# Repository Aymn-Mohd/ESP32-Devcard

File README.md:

# ESP32DevCard v1 — Credit-Card Sized Powerhouse

A deployment-oriented ESP32-S3 development board for engineers building systems, not desk toys. Real power delivery, integrated sensing, and full breakout in a compact 70 × 50 mm footprint.

The goal: eliminate the wiring mess that causes 80% of prototype failures.

---

## Why This Exists

Most ESP32 boards assume your prototype ends at a breadboard. The moment you attach motors, LED arrays, or anything drawing real current, they fall apart.

This solves that problem directly:

* 4-layer stackup for signal and power integrity
* Multiple power injection points
* Clean grounding discipline and ESD protection
* On-board peripheral support for validation without external modules

This is the board you use when reliability matters from the first test.

---

## Core Capabilities

* ESP32-S3-MINI-1-N8 (Wi-Fi + BLE, dual core)
* ENS210 temperature/humidity sensor (I²C)
* WS2812B RGB indicator (GPIO48)
* USB-C for power/programming with protection circuitry
* 44 usable GPIOs on dual headers
* High-current 5V and 3.3V rails
* 4-layer PCB for controlled return paths

---

## Technical Specifications

| Parameter         | Value            |
| ----------------- | ---------------- |
| Dimensions        | 70 × 50 mm       |
| Layers            | 4                |
| MCU Flash         | 8 MB             |
| Operating Voltage | 3.3 V            |
| Status LED        | WS2812B (GPIO48) |
| On-board Sensor   | ENS210           |

---

## Getting Started

1. Plug in via USB-C
2. Flash using the ESP-IDF toolchain or PlatformIO
3. Access peripherals immediately (I²C sensor, indicator LED)

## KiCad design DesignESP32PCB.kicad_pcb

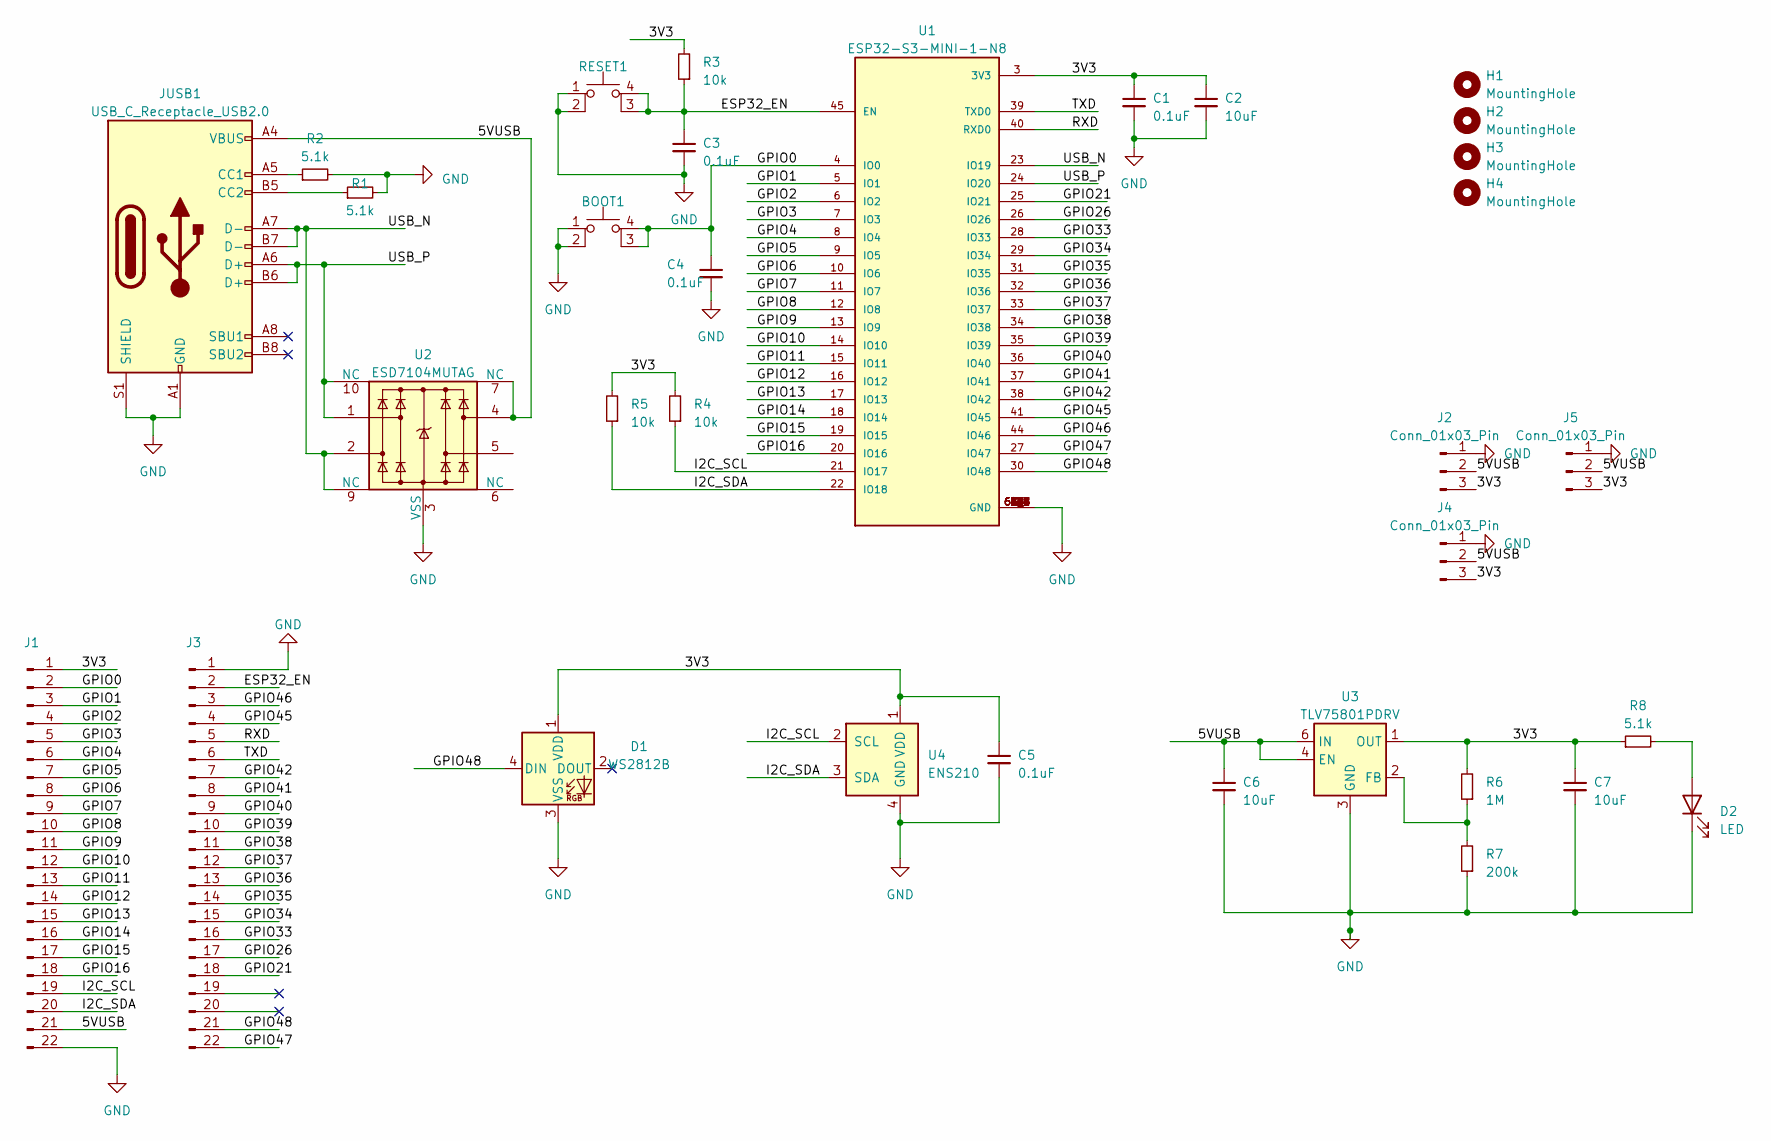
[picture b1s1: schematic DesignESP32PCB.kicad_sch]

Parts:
BOOT1: SW_SPST_PTS810
C1, C3, C4, C5: 0.1uF; C_0603_1608Metric
C2, C6, C7: 10uF; C_0603_1608Metric
D1: WS2812B; LED_WS2812B_PLCC4_5.0x5.0mm_P3.2mm
D2: LED; LED_0603_1608Metric
H1, H2, H3, H4: MountingHole; MountingHole_2.2mm_M2_Pad_Via
J1, J3: PinHeader_1x22_P2.54mm_Vertical
J2, J4, J5: Conn_01x03_Pin; PinHeader_1x03_P2.54mm_Vertical
JUSB1: USB_C_Receptacle_USB2.0; USB_C_Receptacle_GCT_USB4105-xx-A_16P_TopMnt_Horizontal
R1, R2, R8: 5.1k; R_0603_1608Metric
R3, R4, R5: 10k; R_0603_1608Metric
R6: 1M; R_0603_1608Metric
R7: 200k; R_0603_1608Metric
RESET1: SW_SPST_PTS810
U1: ESP32-S3-MINI-1-N8; XCVR_ESP32-S3-MINI-1-N8; PARTREV v0.6
U2: ESD7104MUTAG; Diodes_UDFN-10_1.0x2.5mm_P0.5mm
U3: TLV75801PDRV; WSON-6-1EP_2x2mm_P0.65mm_EP1x1.6mm
U4: ENS210; AMS_QFN-4-1EP_2x2mm_P0.95mm_EP0.7x1.6mm

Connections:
/3V3: C1.1, C2.1, C5.1, C7.1, D1.1 (VDD), J1.1, J2.3, J4.3, J5.3, R3.2, R4.2, R5.2, R6.2, R8.1, U1.3 (3V3), U3.1 (OUT), U4.1 (VDD)
/5VUSB: C6.1, J1.21, J2.2, J4.2, J5.2, JUSB1.A4 (VBUS), JUSB1.A9 (VBUS), JUSB1.B4 (VBUS), JUSB1.B9 (VBUS), U2.4, U2.7 (NC), U3.4 (EN), U3.6 (IN)
/ESP32_EN: C3.1, J3.2, R3.1, RESET1.3 (K), RESET1.4 (A), U1.45 (EN)
/GPIO0: BOOT1.3 (K), BOOT1.4 (A), C4.1, J1.2, U1.4 (IO0)
/GPIO1: J1.3, U1.5 (IO1)
/GPIO2: J1.4, U1.6 (IO2)
/GPIO3: J1.5, U1.7 (IO3)
/GPIO4: J1.6, U1.8 (IO4)
/GPIO5: J1.7, U1.9 (IO5)
/GPIO6: J1.8, U1.10 (IO6)
/GPIO7: J1.9, U1.11 (IO7)
/GPIO8: J1.10, U1.12 (IO8)
/GPIO9: J1.11, U1.13 (IO9)
/GPIO10: J1.12, U1.14 (IO10)
/GPIO11: J1.13, U1.15 (IO11)
/GPIO12: J1.14, U1.16 (IO12)
/GPIO13: J1.15, U1.17 (IO13)
/GPIO14: J1.16, U1.18 (IO14)
/GPIO15: J1.17, U1.19 (IO15)
/GPIO16: J1.18, U1.20 (IO16)
/GPIO21: J3.18, U1.25 (IO21)
/GPIO26: J3.17, U1.26 (IO26)
/GPIO33: J3.16, U1.28 (IO33)
/GPIO34: J3.15, U1.29 (IO34)
/GPIO35: J3.14, U1.31 (IO35)
/GPIO36: J3.13, U1.32 (IO36)
/GPIO37: J3.12, U1.33 (IO37)
/GPIO38: J3.11, U1.34 (IO38)
/GPIO39: J3.10, U1.35 (IO39)
/GPIO40: J3.9, U1.36 (IO40)
/GPIO41: J3.8, U1.37 (IO41)
/GPIO42: J3.7, U1.38 (IO42)
/GPIO45: J3.4, U1.41 (IO45)
/GPIO46: J3.3, U1.44 (IO46)
/GPIO47: J3.22, U1.27 (IO47)
/GPIO48: D1.4 (DIN), J3.21, U1.30 (IO48)
/I2C_SCL: J1.19, R4.1, U1.21 (IO17), U4.2 (SCL)
/I2C_SDA: J1.20, R5.1, U1.22 (IO18), U4.3 (SDA)
/RXD: J3.5, U1.40 (RXD0)
/TXD: J3.6, U1.39 (TXD0)
/USB_N: JUSB1.A7 (D-), JUSB1.B7 (D-), U1.23 (IO19), U2.2, U2.9 (NC)
/USB_P: JUSB1.A6 (D+), JUSB1.B6 (D+), U1.24 (IO20), U2.1, U2.10 (NC)
GND: BOOT1.1, BOOT1.2, C1.2, C2.2, C3.2, C4.2, C5.2, C6.2, C7.2, D1.3 (VSS), D2.1 (K), J1.22, J2.1, J3.1, J4.1, J5.1, JUSB1.A1 (GND), JUSB1.A12 (GND), JUSB1.B1 (GND), JUSB1.B12 (GND), JUSB1.S1 (SHIELD), R1.2, R2.2, R7.1, RESET1.1, RESET1.2, U1.1 (GND), U1.2 (GND), U1.42 (GND), U1.43 (GND), U1.46 (GND), U1.47 (GND), U1.48 (GND), U1.49 (GND), U1.50 (GND), U1.51 (GND), U1.52 (GND), U1.53 (GND), U1.54 (GND), U1.55 (GND), U1.56 (GND), U1.57 (GND), U1.58 (GND), U1.59 (GND), U1.60 (GND), U1.61 (GND), U1.61_1 (GND), U1.61_2 (GND), U1.61_3 (GND), U1.61_4 (GND), U1.61_5 (GND), U1.61_6 (GND), U1.61_7 (GND), U1.61_8 (GND), U1.62 (GND), U1.63 (GND), U1.64 (GND), U1.65 (GND), U2.3 (VSS), U2.8 (VSS), U3.3 (GND), U3.7 (GND), U4.4 (GND), U4.5 (GND)
unnamed: D2.2 (A), R8.2
unnamed: JUSB1.A5 (CC1), R2.1
unnamed: JUSB1.B5 (CC2), R1.1
unnamed: R6.1, R7.2, U3.2 (FB)

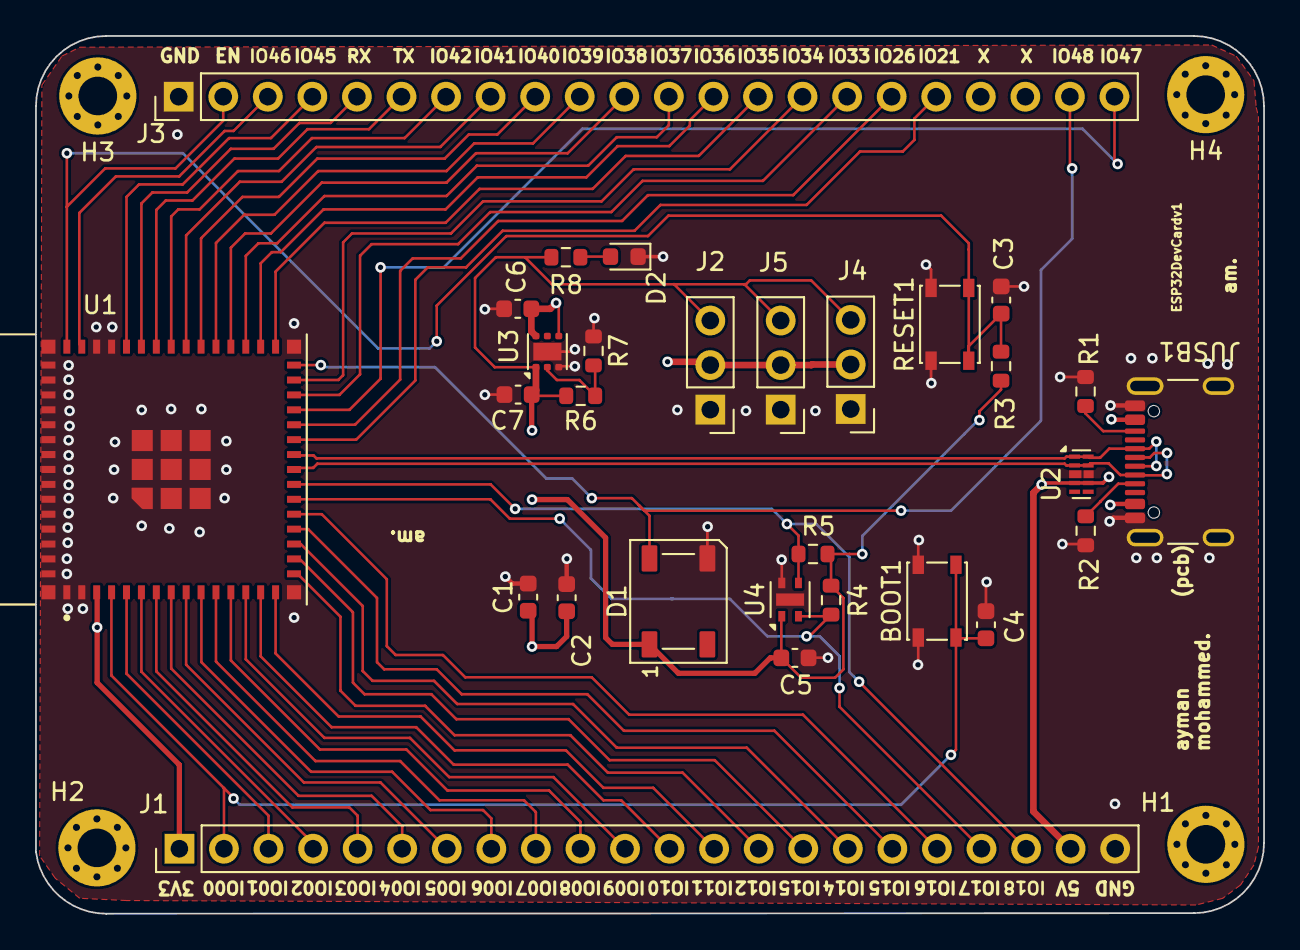
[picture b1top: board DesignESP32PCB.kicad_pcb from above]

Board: 4 copper layers, 70.0 x 50.0 mm, 33 parts (0 on the bottom side), 47 nets.

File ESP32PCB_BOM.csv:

Reference,Qty,Part#,Value,Footprint
U1,1,ESP32-S3-MINI-1-N8,-,ESP32-S3-MINI-1-N8:XCVR_ESP32-S3-MINI-1-N8
U2,1,ESD7104MUTAG,-,Package_DFN_QFN:Diodes_UDFN-10_1.0x2.5mm_P0.5mm
U3,1,TLV75801PDRVR,-,Package_SON:WSON-6-1EP_2x2mm_P0.65mm_EP1x1.6mm
U4,1,ENS210-LQFM,-,Package_DFN_QFN:AMS_QFN-4-1EP_2x2mm_P0.95mm_EP0.7x1.6mm
"BOOT1, RESET1",2,PTS810 SJK 250 SMTR LFS,-,Button_Switch_SMD:SW_SPST_PTS810
JUSB1,1,USB4105-GF-A,-,Connector_USB:USB_C_Receptacle_GCT_USB4105-xx-A_16P_TopMnt_Horizontal
D1,1, COM-16347,-,LED_SMD:LED_WS2812B_PLCC4_5.0x5.0mm_P3.2mm
D2,1,150060RS75000,-,LED_SMD:LED_0603_1608Metric
"J1, J3",2,61302211121,-,Connector_PinHeader_2.54mm:PinHeader_1x22_P2.54mm_Vertical
"C1, C3, C4, C5",4,CC0603KRX7R7BB104,0.1uF,Capacitor_SMD:C_0603_1608Metric
"C2, C6, C7",3,CL10A106MQ8NNNC,10uF,Capacitor_SMD:C_0603_1608Metric
"R1, R2, R8",3,RC0603FR-075K1L,5.1k,Resistor_SMD:R_0603_1608Metric
"R3, R4, R5",3,RC0603FR-0710KL,10k,Resistor_SMD:R_0603_1608Metric
R6,1,RT0603BRD071ML,1M,Resistor_SMD:R_0603_1608Metric
R7,1,RC0603FR-07200KL,200k,Resistor_SMD:R_0603_1608Metric

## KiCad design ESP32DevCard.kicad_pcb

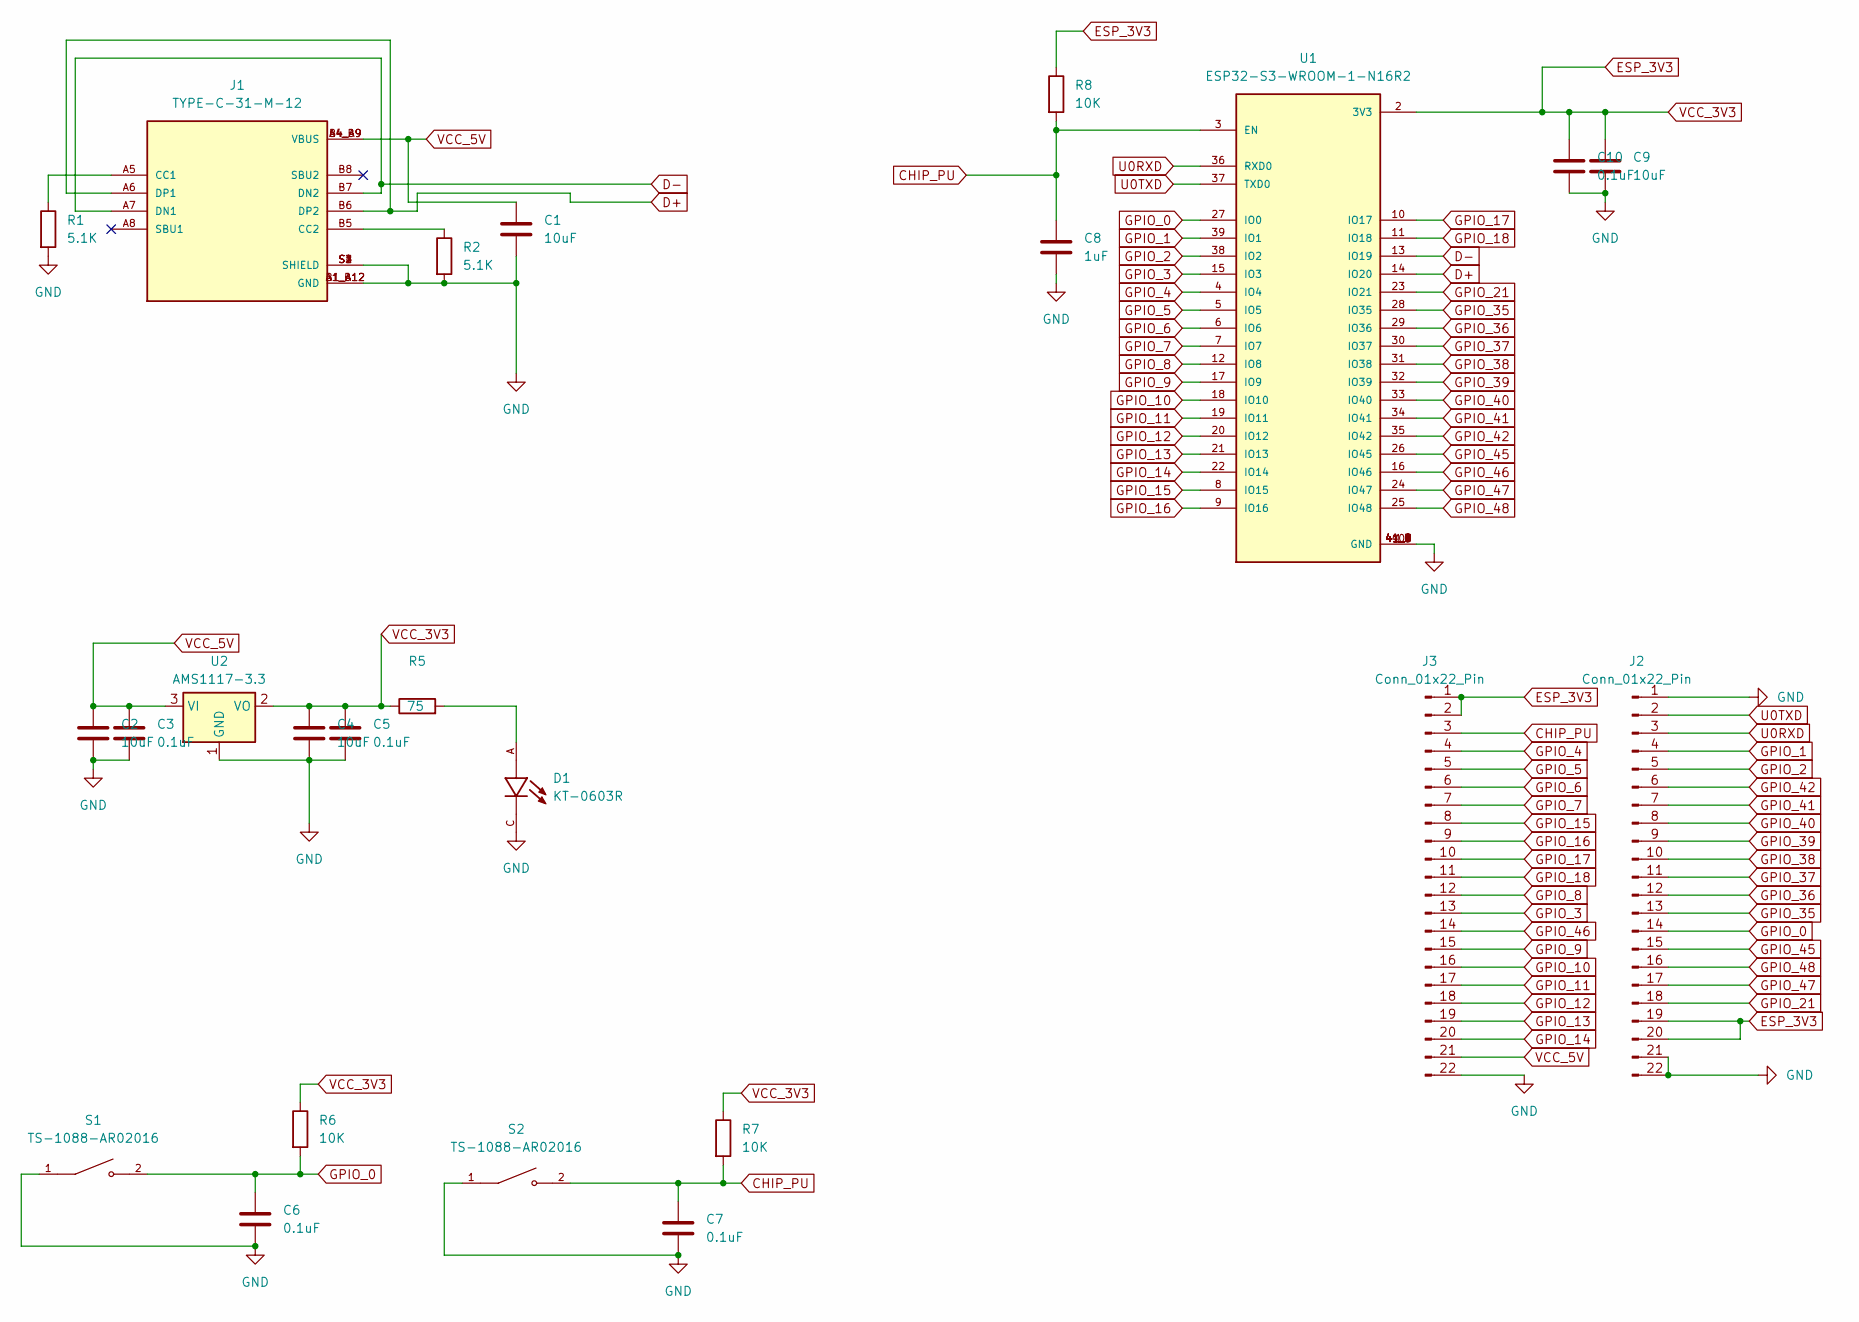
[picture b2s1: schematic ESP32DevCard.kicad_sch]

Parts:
C1, C2, C4, C9: 10uF; CAPC1005X70N
C3, C5, C6, C7, C10: 0.1uF; CAPC1005X55N
C8: 1uF; CAPC1005X55N
D1: KT-0603R; LED_KT-0603R; PARTREV 2013/01/24
J1: TYPE-C-31-M-12; HRO_TYPE-C-31-M-12; PARTREV 2020.12.08
J2, J3: Conn_01x22_Pin; PinHeader_1x22_P1.00mm_Vertical
R1, R2: 5.1K; RESC1005X40N
R5: 75; RESC1608X55N
R6, R7, R8: 10K; RESC3115X65N
S1, S2: TS-1088-AR02016; SW_TS-1088-AR02016; PARTREV N/A
U1: ESP32-S3-WROOM-1-N16R2; XCVR_ESP32-S3-WROOM-1-N16R2; PARTREV v1.0
U2: AMS1117-3.3; SOT229P700X180-4N

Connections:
CHIP_PU: C7.1, C8.1, J3.3, R7.2, R8.2, S2.2, U1.3 (EN)
D+: J1.A6 (DP1), J1.B6 (DP2), U1.14 (IO20)
D-: J1.A7 (DN1), J1.B7 (DN2), U1.13 (IO19)
ESP_3V3: C4.1, C5.1, C9.1, C10.1, J2.19, J2.20, J3.1, J3.2, R5.1, R6.1, R7.1, R8.1, U1.2 (3V3), U2.2 (VO)
GND: C1.2, C2.2, C3.2, C4.2, C5.2, C6.2, C7.2, C8.2, C9.2, C10.2, D1.C, J1.A1_B12 (GND), J1.B1_A12 (GND), J1.S1 (SHIELD), J1.S2 (SHIELD), J1.S3 (SHIELD), J1.S4 (SHIELD), J2.1, J2.21, J2.22, J3.22, R1.2, R2.2, S1.1, S2.1, U1.1 (GND), U1.40 (GND), U1.41_1 (GND), U1.41_2 (GND), U1.41_3 (GND), U1.41_4 (GND), U1.41_5 (GND), U1.41_6 (GND), U1.41_7 (GND), U1.41_8 (GND), U1.41_9 (GND), U2.1 (GND)
GPIO_0: C6.1, J2.14, R6.2, S1.2, U1.27 (IO0)
GPIO_1: J2.4, U1.39 (IO1)
GPIO_2: J2.5, U1.38 (IO2)
GPIO_3: J3.13, U1.15 (IO3)
GPIO_4: J3.4, U1.4 (IO4)
GPIO_5: J3.5, U1.5 (IO5)
GPIO_6: J3.6, U1.6 (IO6)
GPIO_7: J3.7, U1.7 (IO7)
GPIO_8: J3.12, U1.12 (IO8)
GPIO_9: J3.15, U1.17 (IO9)
GPIO_10: J3.16, U1.18 (IO10)
GPIO_11: J3.17, U1.19 (IO11)
GPIO_12: J3.18, U1.20 (IO12)
GPIO_13: J3.19, U1.21 (IO13)
GPIO_14: J3.20, U1.22 (IO14)
GPIO_15: J3.8, U1.8 (IO15)
GPIO_16: J3.9, U1.9 (IO16)
GPIO_17: J3.10, U1.10 (IO17)
GPIO_18: J3.11, U1.11 (IO18)
GPIO_21: J2.18, U1.23 (IO21)
GPIO_35: J2.13, U1.28 (IO35)
GPIO_36: J2.12, U1.29 (IO36)
GPIO_37: J2.11, U1.30 (IO37)
GPIO_38: J2.10, U1.31 (IO38)
GPIO_39: J2.9, U1.32 (IO39)
GPIO_40: J2.8, U1.33 (IO40)
GPIO_41: J2.7, U1.34 (IO41)
GPIO_42: J2.6, U1.35 (IO42)
GPIO_45: J2.15, U1.26 (IO45)
GPIO_46: J3.14, U1.16 (IO46)
GPIO_47: J2.17, U1.24 (IO47)
GPIO_48: J2.16, U1.25 (IO48)
unnamed: D1.A, R5.2
unnamed: J1.A5 (CC1), R1.1
unnamed: J1.B5 (CC2), R2.1
U0RXD: J2.3, U1.36 (RXD0)
U0TXD: J2.2, U1.37 (TXD0)
VCC_5V: C1.1, C2.1, C3.1, J1.A4_B9 (VBUS), J1.B4_A9 (VBUS), J3.21, U2.3 (VI)

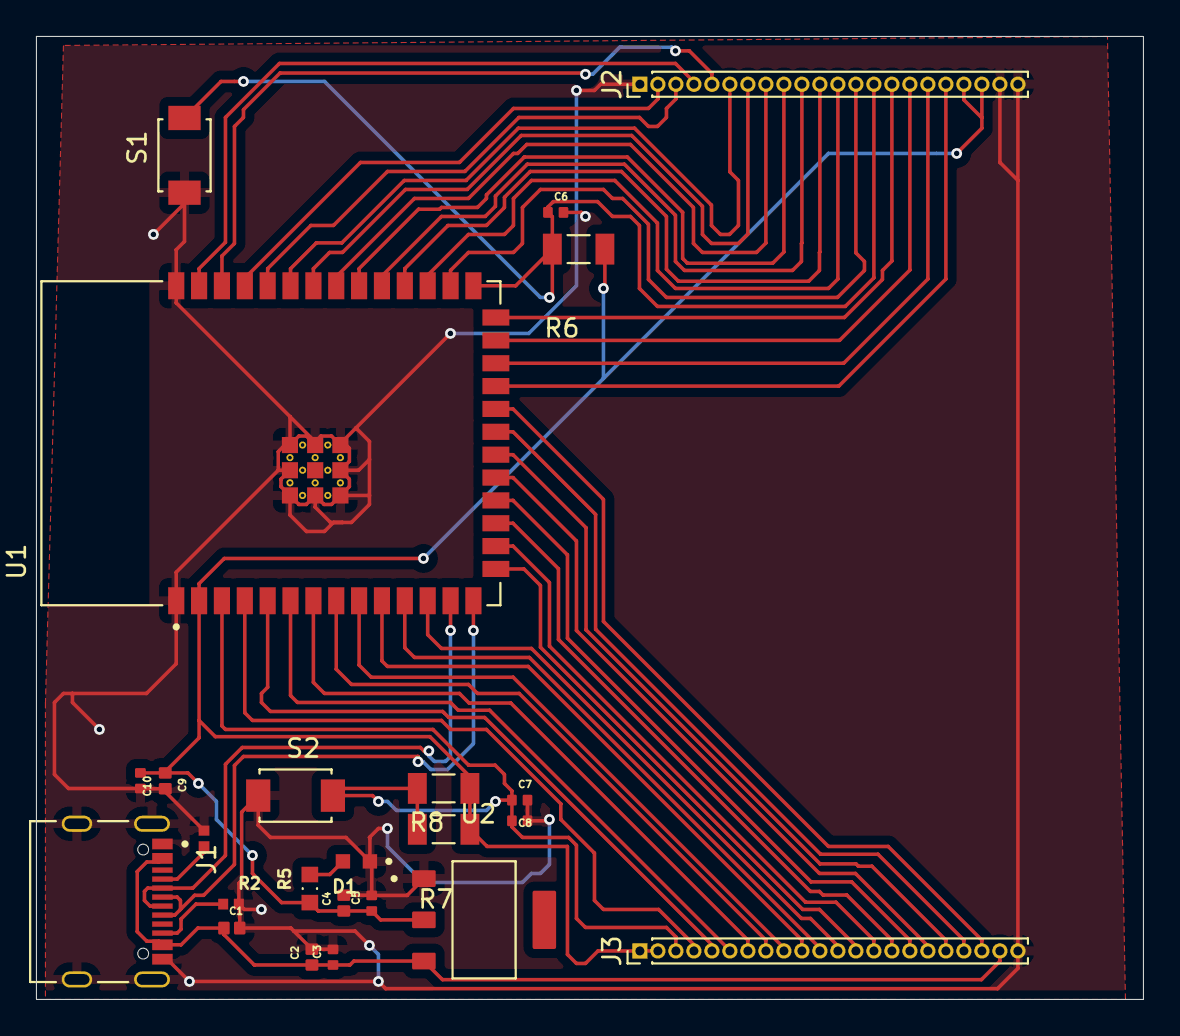
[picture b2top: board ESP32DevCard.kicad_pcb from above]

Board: 2 copper layers, 61.5 x 53.5 mm, 24 parts (0 on the bottom side), 43 nets.

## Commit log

2025-12-28 Add README for ESP32DevCard v1
    Added detailed information about the ESP32DevCard v1, including its capabilities, technical specifications, and getting started instructions.
